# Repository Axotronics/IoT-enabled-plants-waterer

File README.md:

# IoT-enabled-plants-waterer
It is an IoT enabled Plants waterer. 
The materials used in the above project are:
a) NodeMCU 1.0 ESP8266 WiFi Dev Board.
b) Generic Relay Module
c) Soil Moisture Sensor
d) Motor used to raise water

Working of the project:
a) First, the node mcu will connect itself to a local WiFi network. Please change the name to your wifi ssid from myssid. Do the same with the password too.
b) Create a webhook on https://maker.ifttt.com, go to the documentation and copy the api key and paste it in the ifttt_api_key variable.
c) The basic working principle of this project is that if the moisture in the soil sensor is high, the relay module will turn on and supply high voltage of current to the connected motor.
While the motor is on, it will give you a notification or a call on your device that the motor is on now.

For any further queries kindly contact me on akshayvr2@gmail.com

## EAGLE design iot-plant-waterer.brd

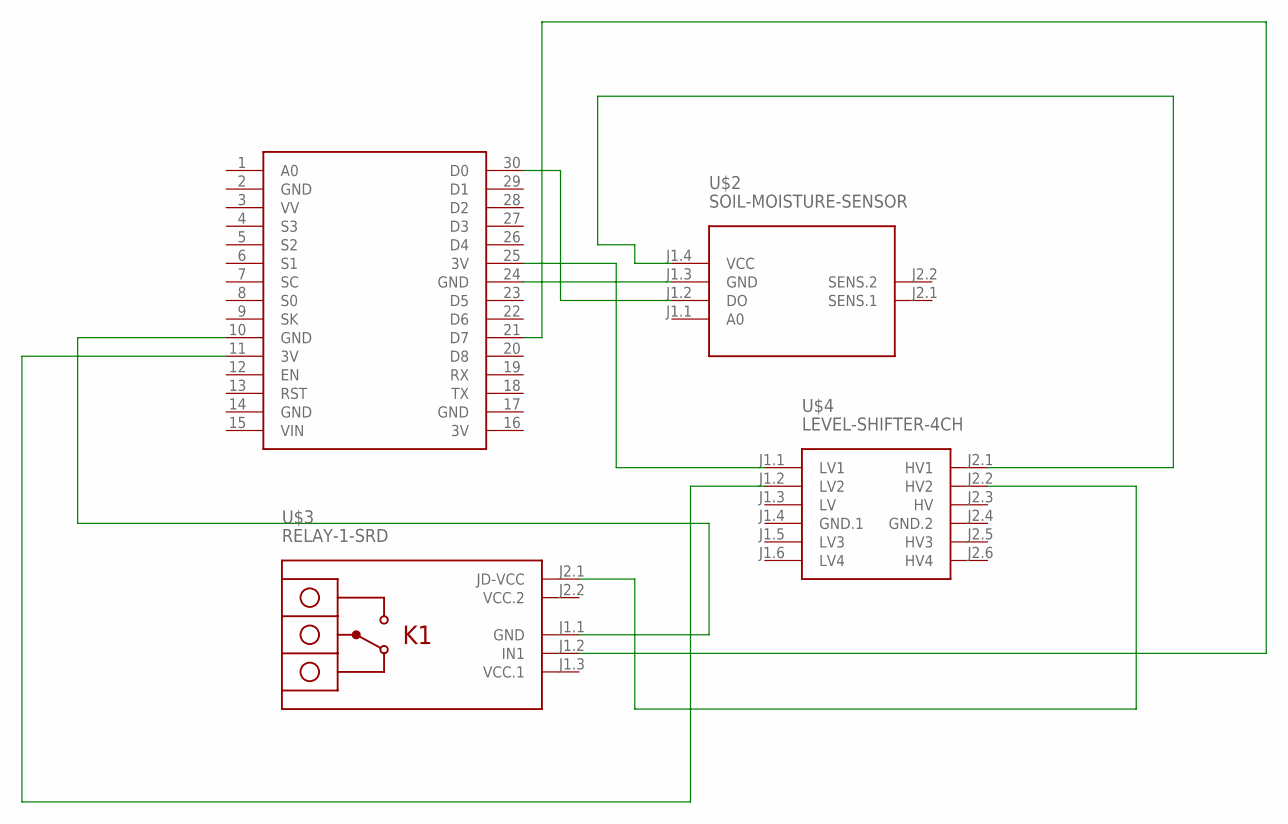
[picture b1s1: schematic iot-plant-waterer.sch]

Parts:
U$1: NODEMCU
U$2: SOIL-MOISTURE-SENSOR
U$3: RELAY-1-SRD
U$4: LEVEL-SHIFTER-4CH

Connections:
3V: U$1.16 (3V)
GND: U$1.2 (GND), U$1.14 (GND), U$1.17 (GND)
GND.1: U$4.J1.4 (GND.1)
GND.2: U$4.J2.4 (GND.2)
HV: U$4.J2.3 (HV)
LV: U$4.J1.3 (LV)
unnamed: U$1.25 (3V), U$4.J1.1 (LV1)
unnamed: U$2.J1.4 (VCC), U$4.J2.1 (HV1)
unnamed: U$1.24 (GND), U$2.J1.3 (GND)
unnamed: U$1.30 (D0), U$2.J1.2 (DO)
unnamed: U$1.11 (3V), U$4.J1.2 (LV2)
unnamed: U$3.J2.1 (JD-VCC), U$4.J2.2 (HV2)
unnamed: U$1.10 (GND), U$3.J1.1 (GND)
unnamed: U$1.21 (D7), U$3.J1.2 (IN1)
VCC.1: U$3.J1.3 (VCC.1)
VCC.2: U$3.J2.2 (VCC.2)

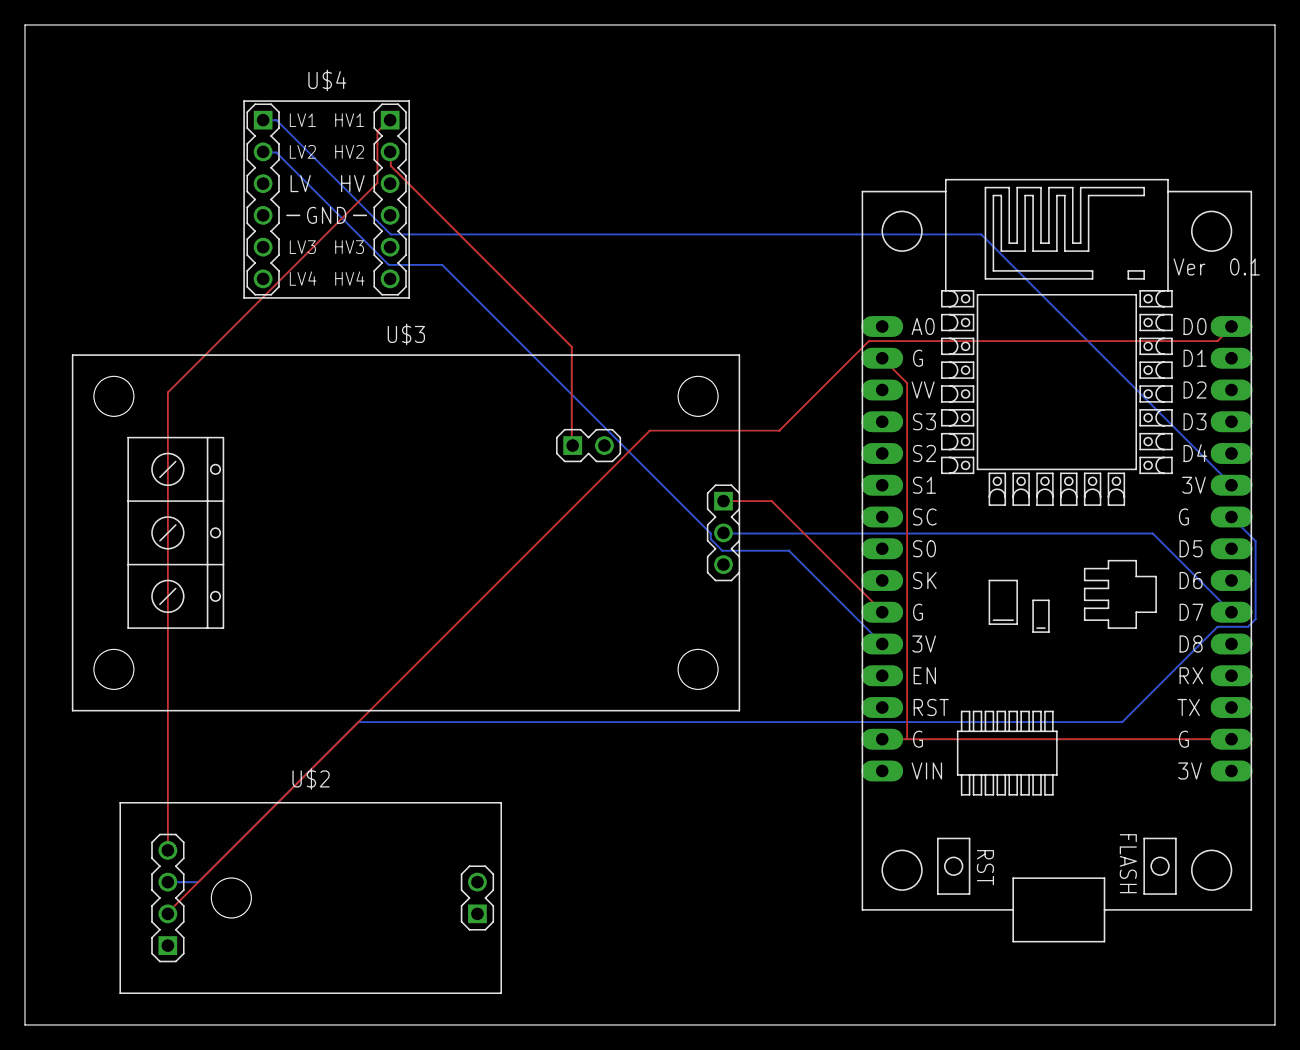
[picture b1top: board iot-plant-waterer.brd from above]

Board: 2 copper layers, 100.0 x 80.0 mm, 4 parts (0 on the bottom side), 9 nets.

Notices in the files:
parts and their libraries:
diy-modules: Released under the Creative Commons Attribution 4.0 International License: http://creativecommons.org/licenses/by/4.0
